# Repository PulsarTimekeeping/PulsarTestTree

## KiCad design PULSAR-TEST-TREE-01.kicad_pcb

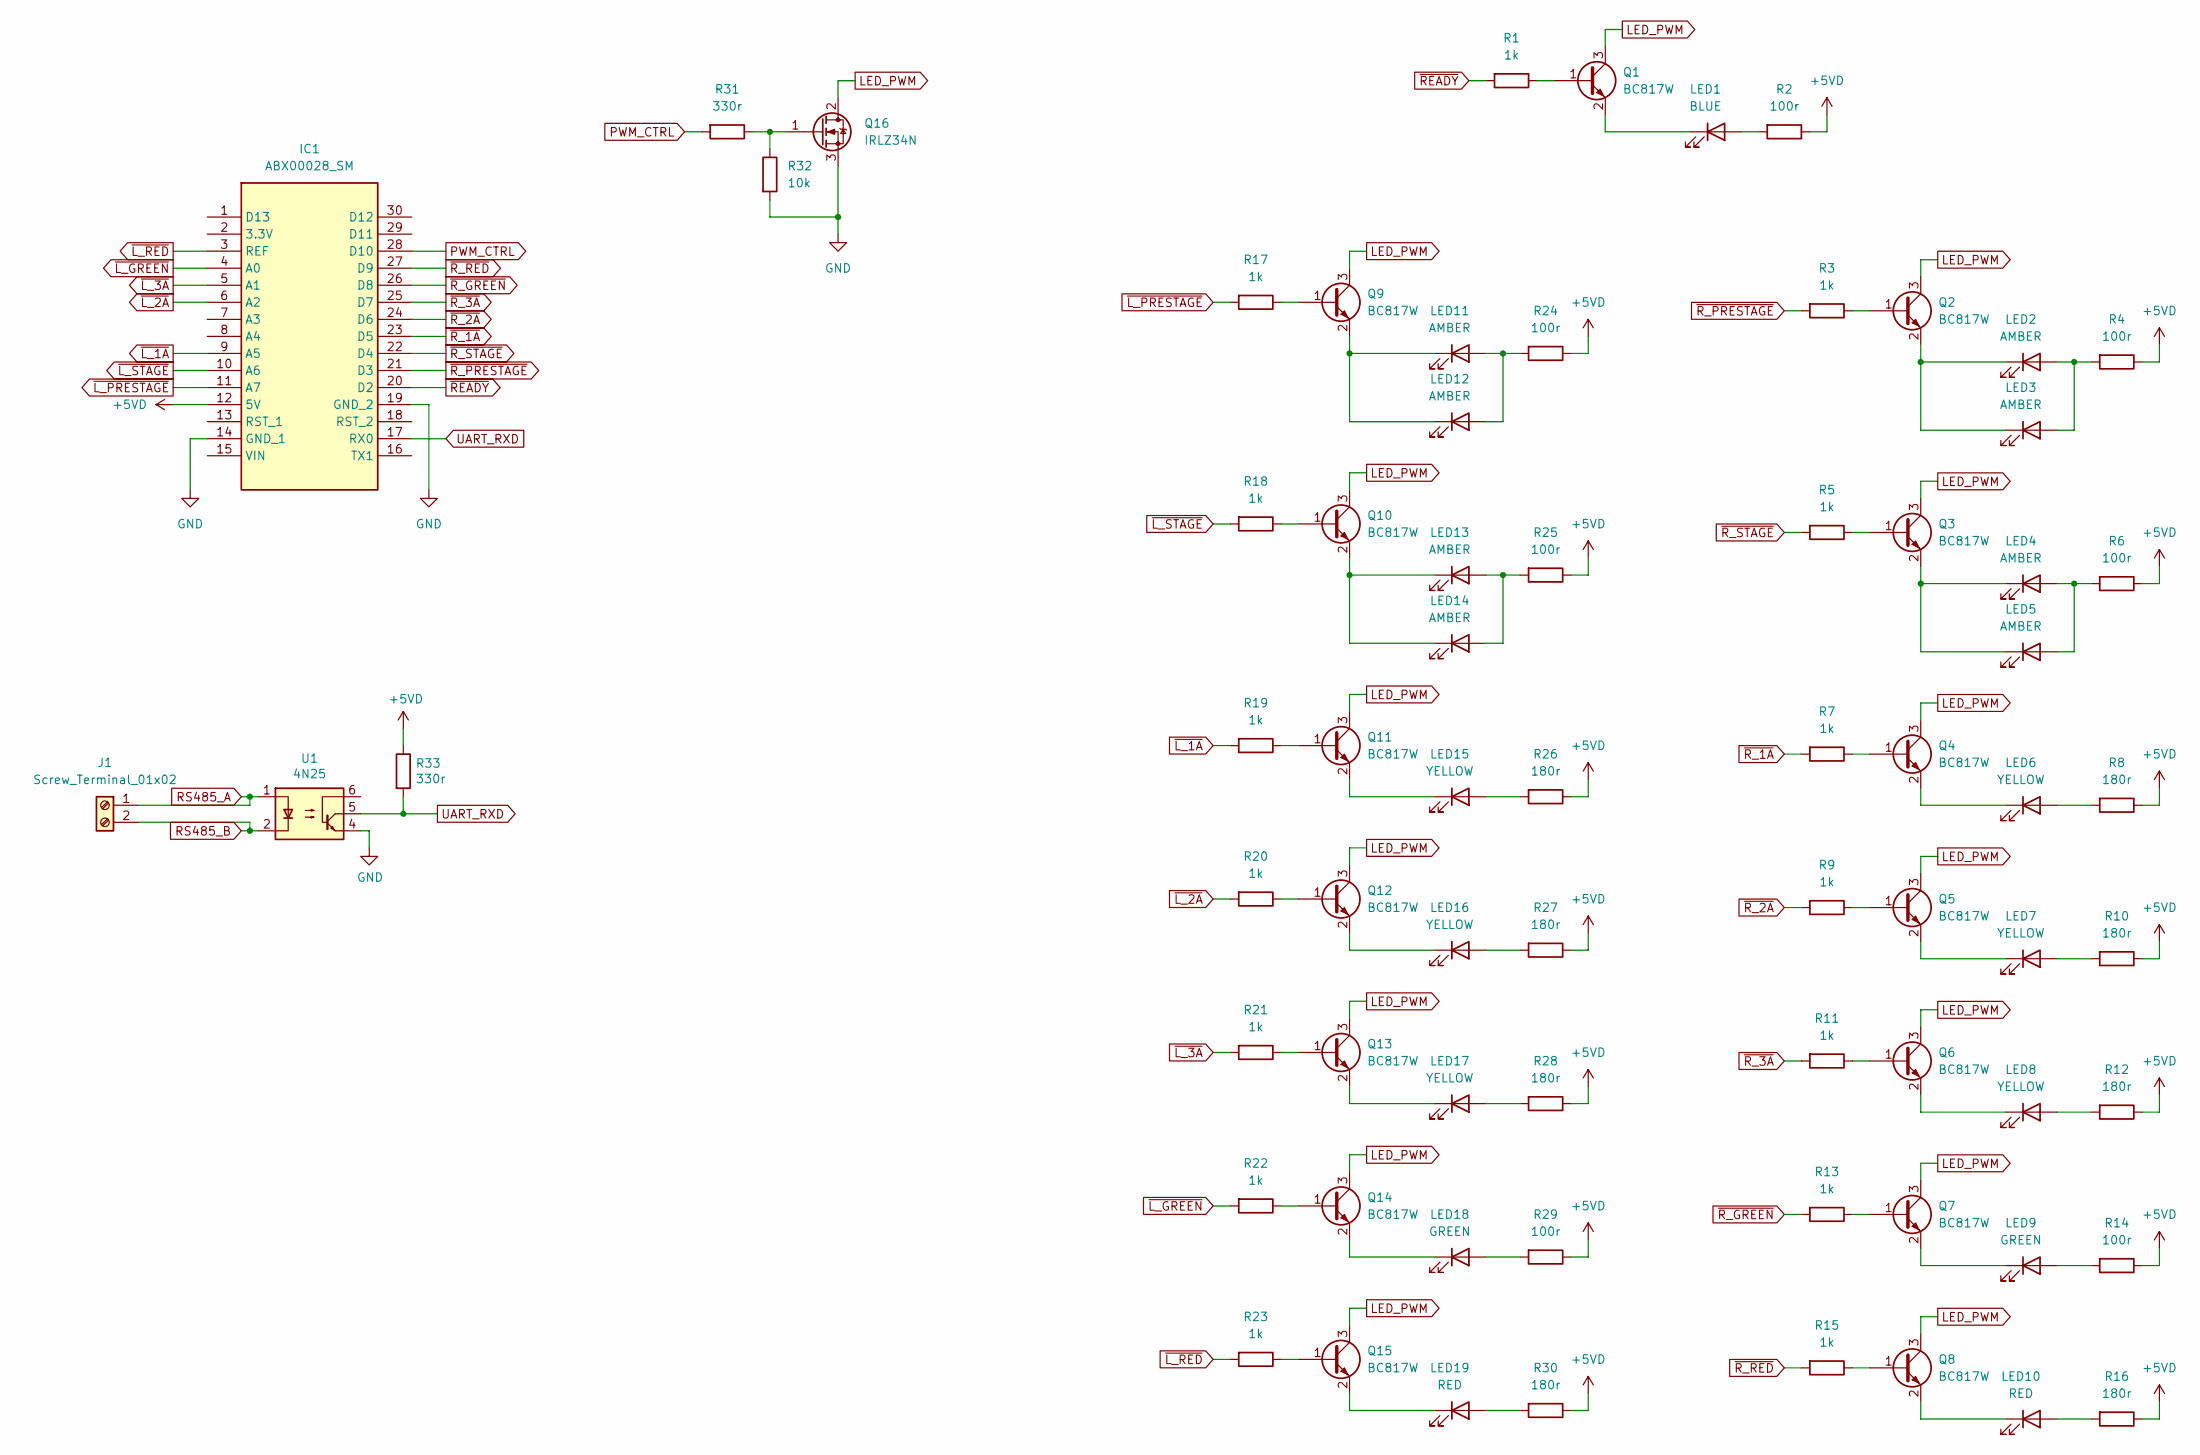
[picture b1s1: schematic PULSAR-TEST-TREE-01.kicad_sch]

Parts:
IC1: ABX00028_SM; Manufacturer_Part_Number ABX00028; Mouser Part Number 782-ABX00028
J1: Screw_Terminal_01x02; TerminalBlock_RND_205-00045_1x02_P5.00mm_Horizontal
LED1: BLUE; LED_D5.0mm
LED2, LED3, LED4, LED5, LED11, LED12, LED13, LED14: AMBER; LED_D5.0mm
LED6, LED7, LED8, LED15, LED16, LED17: YELLOW; LED_D10.0mm
LED9, LED18: GREEN; LED_D10.0mm
LED10, LED19: RED; LED_D10.0mm
Q1, Q2, Q3, Q4, Q5, Q6, Q7, Q8, Q9, Q10, Q11, Q12, Q13, Q14, Q15: BC817W; SOT-323_SC-70
Q16: IRLZ34N; TO-220-3_Vertical
R1, R3, R5, R7, R9, R11, R13, R15, R17, R18, R19, R20, R21, R22, R23: 1k; R_1206_3216Metric_Pad1.30x1.75mm_HandSolder
R2, R4, R6, R14, R24, R25, R29: 100r; R_1206_3216Metric_Pad1.30x1.75mm_HandSolder
R8, R10, R12, R16, R26, R27, R28, R30: 180r; R_1206_3216Metric_Pad1.30x1.75mm_HandSolder
R31, R33: 330r; R_1206_3216Metric_Pad1.30x1.75mm_HandSolder
R32: 10k; R_1206_3216Metric_Pad1.30x1.75mm_HandSolder
U1: 4N25; DIP-6_W7.62mm

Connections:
+5VD: IC1.12 (5V), R2.1, R4.1, R6.1, R8.1, R10.1, R12.1, R14.1, R16.1, R24.1, R25.1, R26.1, R27.1, R28.1, R29.1, R30.1, R33.1
GND: IC1.14 (GND_1), IC1.19 (GND_2), Q16.3 (S), R32.2, U1.4
LED_PWM: Q1.3 (C), Q2.3 (C), Q3.3 (C), Q4.3 (C), Q5.3 (C), Q6.3 (C), Q7.3 (C), Q8.3 (C), Q9.3 (C), Q10.3 (C), Q11.3 (C), Q12.3 (C), Q13.3 (C), Q14.3 (C), Q15.3 (C), Q16.2 (D)
unnamed: LED1.2 (A), R2.2
unnamed: LED1.1 (K), Q1.2 (E)
unnamed: LED2.2 (A), LED3.2 (A), R4.2
unnamed: LED2.1 (K), LED3.1 (K), Q2.2 (E)
unnamed: LED4.2 (A), LED5.2 (A), R6.2
unnamed: LED4.1 (K), LED5.1 (K), Q3.2 (E)
unnamed: LED6.2 (A), R8.2
unnamed: LED6.1 (K), Q4.2 (E)
unnamed: LED7.2 (A), R10.2
unnamed: LED7.1 (K), Q5.2 (E)
unnamed: LED8.2 (A), R12.2
unnamed: LED8.1 (K), Q6.2 (E)
unnamed: LED9.2 (A), R14.2
unnamed: LED9.1 (K), Q7.2 (E)
unnamed: LED10.2 (A), R16.2
unnamed: LED10.1 (K), Q8.2 (E)
unnamed: LED11.2 (A), LED12.2 (A), R24.2
unnamed: LED11.1 (K), LED12.1 (K), Q9.2 (E)
unnamed: LED13.2 (A), LED14.2 (A), R25.2
unnamed: LED13.1 (K), LED14.1 (K), Q10.2 (E)
unnamed: LED15.2 (A), R26.2
unnamed: LED15.1 (K), Q11.2 (E)
unnamed: LED16.2 (A), R27.2
unnamed: LED16.1 (K), Q12.2 (E)
unnamed: LED17.2 (A), R28.2
unnamed: LED17.1 (K), Q13.2 (E)
unnamed: LED18.2 (A), R29.2
unnamed: LED18.1 (K), Q14.2 (E)
unnamed: LED19.2 (A), R30.2
unnamed: LED19.1 (K), Q15.2 (E)
unnamed: Q1.1 (B), R1.1
unnamed: Q2.1 (B), R3.1
unnamed: Q3.1 (B), R5.1
unnamed: Q4.1 (B), R7.1
unnamed: Q5.1 (B), R9.1
unnamed: Q6.1 (B), R11.1
unnamed: Q7.1 (B), R13.1
unnamed: Q8.1 (B), R15.1
unnamed: Q9.1 (B), R17.1
unnamed: Q10.1 (B), R18.1
unnamed: Q11.1 (B), R19.1
unnamed: Q12.1 (B), R20.1
unnamed: Q13.1 (B), R21.1
unnamed: Q14.1 (B), R22.1
unnamed: Q15.1 (B), R23.1
unnamed: Q16.1 (G), R31.1, R32.1
PWM_CTRL: IC1.28 (D10), R31.2
RS485_A: J1.1, U1.1
RS485_B: J1.2, U1.2
UART_RXD: IC1.17 (RX0), R33.2, U1.5
~L_1A: IC1.9 (A5), R19.2
~L_2A: IC1.6 (A2), R20.2
~L_3A: IC1.5 (A1), R21.2
~L_GREEN: IC1.4 (A0), R22.2
~L_PRESTAGE: IC1.11 (A7), R17.2
~L_RED: IC1.3 (REF), R23.2
~L_STAGE: IC1.10 (A6), R18.2
~READY: IC1.20 (D2), R1.2
~R_1A: IC1.23 (D5), R7.2
~R_2A: IC1.24 (D6), R9.2
~R_3A: IC1.25 (D7), R11.2
~R_GREEN: IC1.26 (D8), R13.2
~R_PRESTAGE: IC1.21 (D3), R3.2
~R_RED: IC1.27 (D9), R15.2
~R_STAGE: IC1.22 (D4), R5.2

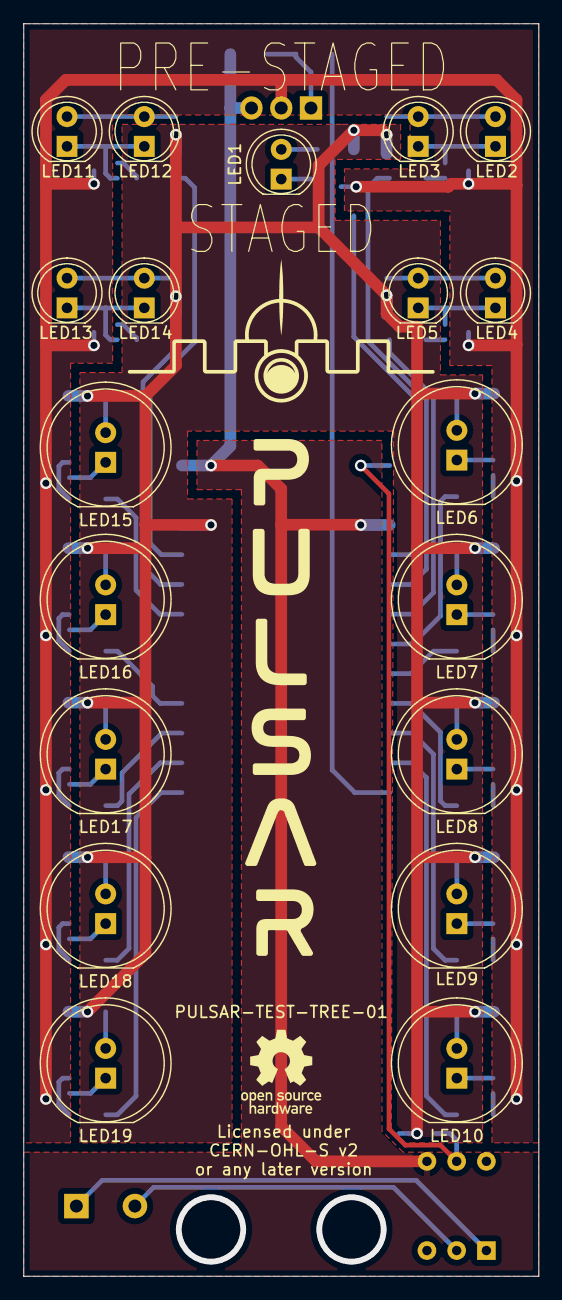
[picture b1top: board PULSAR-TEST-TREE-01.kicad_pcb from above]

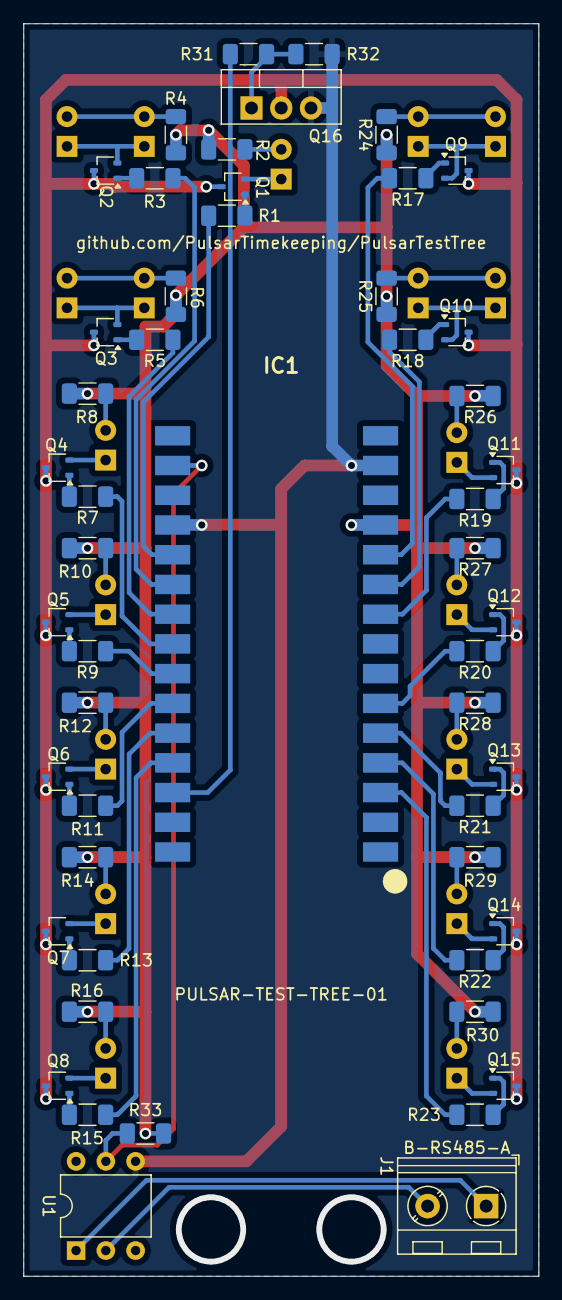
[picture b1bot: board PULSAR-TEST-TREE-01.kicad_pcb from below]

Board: 2 copper layers, 44.0 x 107.0 mm, 71 parts (52 on the bottom side), 68 nets.

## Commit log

2025-02-19 Create LICENSE
2025-03-08 Add files via upload
    Initial commit. Completed schematic, PCB design and manufacturing data.

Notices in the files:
PULSAR-TEST-TREE-01.kicad_pcb:
Licensed under
CERN-OHL-S v2
Copyright David Anniwell 2025.
This source describes Open Hardware and is licensed under the CERN-
under the terms of the CERN-OHL-S v2
(https://ohwr.org/cern ohl s v2.txt ).
QUALITY AND FITNESS FOR A PARTICULAR PURPOSE. Please see
the CERN-OHL-S v2 for applicable conditions.
As per CERN-OHL-S v2 section 4, should You produce hardware based
